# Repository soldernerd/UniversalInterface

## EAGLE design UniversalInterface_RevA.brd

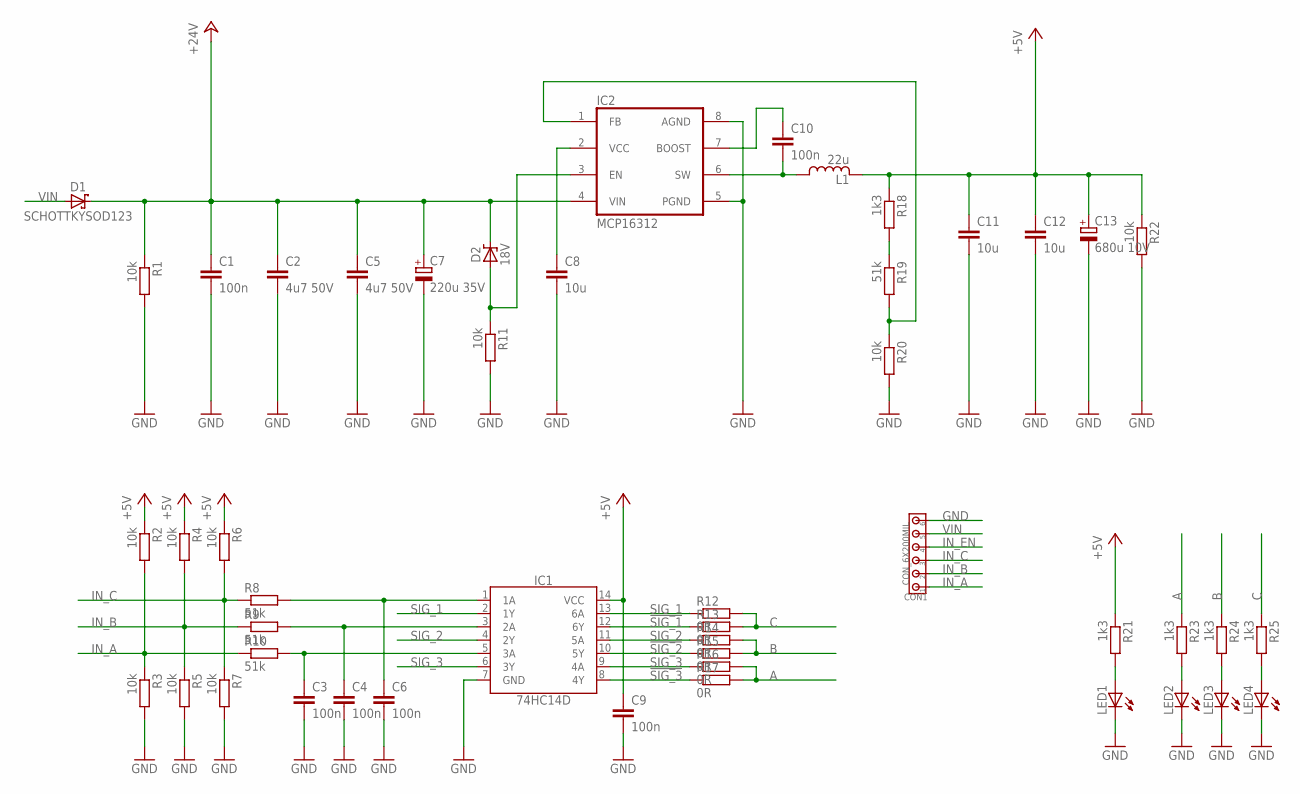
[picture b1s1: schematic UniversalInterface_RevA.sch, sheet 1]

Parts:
C1, C3, C4, C6, C9, C10: 100n; C0805
C2, C5: 4u7 50V; C1206
C7: 220u 35V; 8MM
C8, C11, C12: 10u; C0805
C13: 680u 10V; 8MM
CON1: CON_6X200MIL; 200MIL_6X
D1: SCHOTTKYSOD123; SOD123
D2: 18V; SOD323
IC1: 74HC14D; SO14
IC2: MCP16312; MSOP8
L1: 22u; LPS4018
LED1, LED2, LED3, LED4: LED0805_NB; LED0805_NOBOARDER
R1, R2, R3, R4, R5, R6, R7, R11, R20, R22: 10k; R0805
R8, R9, R10, R19: 51k; R0805
R12, R13, R14, R15, R16, R17: 0R; R0805
R18, R21, R23, R24, R25: 1k3; R0805

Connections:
!SIG_1!: IC1.12 (6Y), R13.1
!SIG_2!: IC1.10 (5Y), R15.1
!SIG_3!: IC1.8 (4Y), R17.1
+5V: C9.1, C11.1, C12.1, C13.+, IC1.14 (VCC), L1.2, R2.1, R4.1, R6.1, R18.1, R21.1, R22.1; also elsewhere on the board
+24V: C1.1, C2.1, C5.1, C7.+, D1.C, D2.C, IC2.4 (VIN), R1.1; also elsewhere on the board
A: R16.2, R17.2, R23.1; also elsewhere on the board
B: R14.2, R15.2, R24.1; also elsewhere on the board
BOOST: C10.1, IC2.7 (BOOST)
C: R12.2, R13.2, R25.1; also elsewhere on the board
FOO: C3.1, IC1.5 (3A), R10.2
GND: C1.2, C2.2, C3.2, C4.2, C5.2, C6.2, C7.-, C8.2, C9.2, C11.2, C12.2, C13.-, CON1.6, IC1.7 (GND), IC2.5 (PGND), IC2.8 (AGND), LED1.C, LED2.C, LED3.C, LED4.C, R1.2, R3.2, R5.2, R7.2, R11.2, R20.2, R22.2; also elsewhere on the board
IN_A: CON1.1, R2.2, R3.1, R10.1
IN_B: CON1.2, R4.2, R5.1, R9.1
IN_C: CON1.3, R6.2, R7.1, R8.1
IN_EN: CON1.4; also elsewhere on the board
unnamed: IC2.1 (FB), R19.2, R20.1
unnamed: LED1.A, R21.2
unnamed: D2.A, IC2.3 (EN), R11.1
unnamed: R18.2, R19.1
unnamed: C8.1, IC2.2 (VCC)
unnamed: LED2.A, R23.2
unnamed: LED3.A, R24.2
unnamed: LED4.A, R25.2
unnamed: C6.1, IC1.1 (1A), R8.2
unnamed: C4.1, IC1.3 (2A), R9.2
SIG_1: IC1.2 (1Y), IC1.13 (6A), R12.1
SIG_2: IC1.4 (2Y), IC1.11 (5A), R14.1
SIG_3: IC1.6 (3Y), IC1.9 (4A), R16.1
SWITCH: C10.2, IC2.6 (SW), L1.1
VIN: CON1.5, D1.A

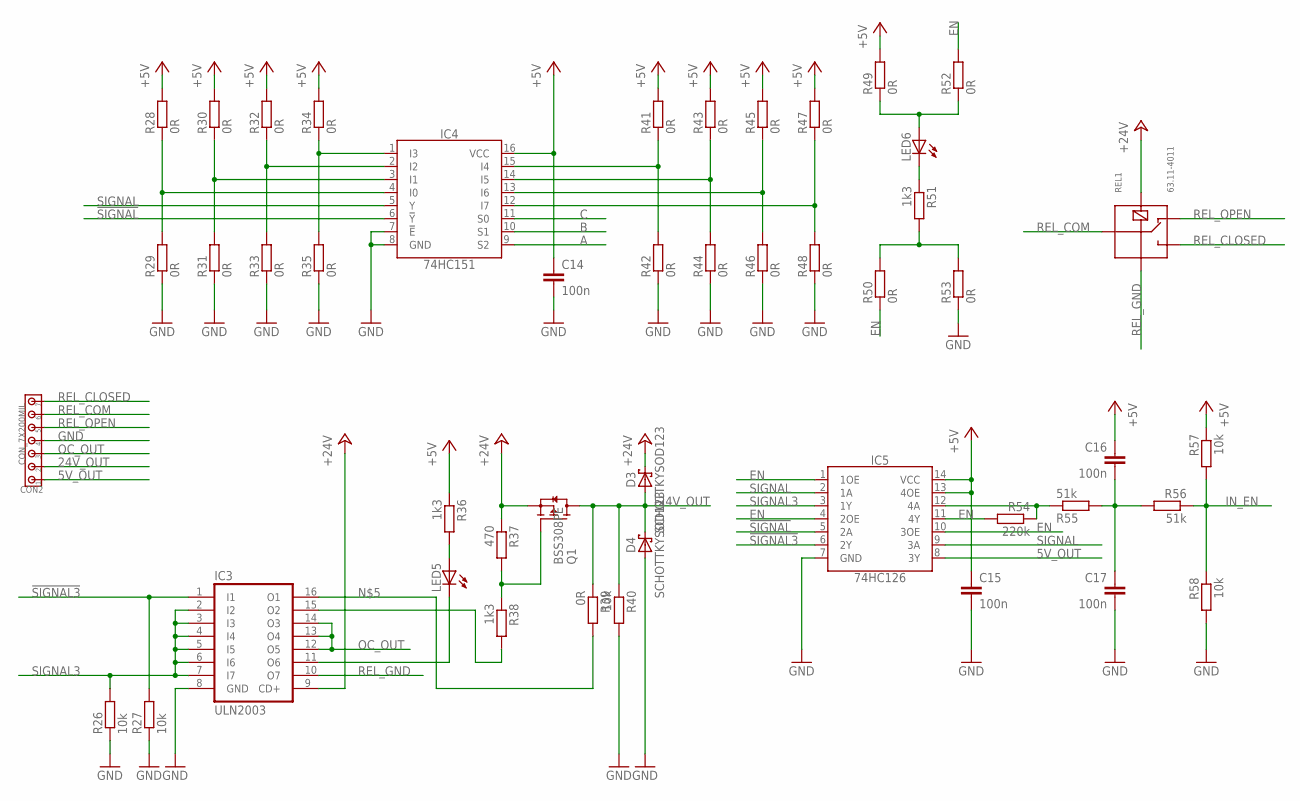
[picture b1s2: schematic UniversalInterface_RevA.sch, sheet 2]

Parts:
C14, C15, C16, C17: 100n; C0805
CON2: CON_7X200MIL; 200MIL_7X
D3, D4: SCHOTTKYSOD123; SOD123
IC3: ULN2003; SO16
IC4: 74HC151; SO16
IC5: 74HC126; SO14
LED5, LED6: LED0805_NB; LED0805_NOBOARDER
Q1: BSS308PE; SOT23
R26, R27, R40, R57, R58: 10k; R0805
R28, R29, R30, R31, R32, R33, R34, R35, R41, R42, R43, R44, R45, R46, R47, R48: 0R; R0805_NOSILK
R36, R38, R51: 1k3; R0805
R37: 470; R0805
R39, R49, R50, R52, R53: 0R; R0805
R54: 220k; R0805
R55, R56: 51k; R0805
REL1: 63.11-4011; G5LE

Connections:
5V_OUT: CON2.1, IC5.8 (3Y)
24V_OUT: CON2.2, D3.A, D4.C, Q1.3 (D), R39.1, R40.1
!SIGNAL3!: IC3.1 (I1), IC5.6 (2Y), R27.2
!SIGNAL!: IC4.6 (!Y!), IC5.5 (2A)
+5V: C14.1, C15.1, C16.1, IC4.16 (VCC), IC5.13 (4OE), IC5.14 (VCC), R28.2, R30.2, R32.2, R34.2, R36.1, R41.2, R43.2, R45.2, R47.2, R49.2, R57.1; also elsewhere on the board
+24V: D3.C, IC3.9 (CD+), Q1.2 (S), R37.1, REL1.2; also elsewhere on the board
A: IC4.9 (S2); also elsewhere on the board
B: IC4.10 (S1); also elsewhere on the board
C: IC4.11 (S0); also elsewhere on the board
EN: IC5.1 (1OE), IC5.4 (2OE), IC5.10 (3OE), IC5.11 (4Y), R50.1, R52.2, R54.2
GND: C14.2, C15.2, C17.2, CON2.4, D4.A, IC3.8 (GND), IC4.7 (!E!), IC4.8 (GND), IC5.7 (GND), R26.1, R27.1, R29.1, R31.1, R33.1, R35.1, R40.2, R42.1, R44.1, R46.1, R48.1, R53.1, R58.2; also elsewhere on the board
I0: IC4.4 (I0), R28.1, R29.2
I1: IC4.3 (I1), R30.1, R31.2
I2: IC4.2 (I2), R32.1, R33.2
I3: IC4.1 (I3), R34.1, R35.2
I4: IC4.15 (I4), R41.1, R42.2
I5: IC4.14 (I5), R43.1, R44.2
I6: IC4.13 (I6), R45.1, R46.2
I7: IC4.12 (I7), R47.1, R48.2
IN_EN: R56.1, R57.2, R58.1; also elsewhere on the board
unnamed: C16.2, C17.1, R55.2, R56.2
unnamed: LED6.C, R51.1
unnamed: IC3.16 (O1), R39.2
unnamed: IC3.11 (O6), LED5.C
unnamed: IC5.12 (4A), R54.1, R55.1
unnamed: LED6.A, R49.1, R52.1
unnamed: LED5.A, R36.2
unnamed: Q1.1 (G), R37.2, R38.1
unnamed: IC3.15 (O2), R38.2
unnamed: R50.2, R51.2, R53.2
OC_OUT: CON2.3, IC3.12 (O5), IC3.13 (O4), IC3.14 (O3)
REL_CLOSED: CON2.7, REL1.C
REL_COM: CON2.6, REL1.COM
REL_GND: IC3.10 (O7), REL1.1
REL_OPEN: CON2.5, REL1.O
SIGNAL: IC4.5 (Y), IC5.2 (1A), IC5.9 (3A)
SIGNAL3: IC3.2 (I2), IC3.3 (I3), IC3.4 (I4), IC3.5 (I5), IC3.6 (I6), IC3.7 (I7), IC5.3 (1Y), R26.2

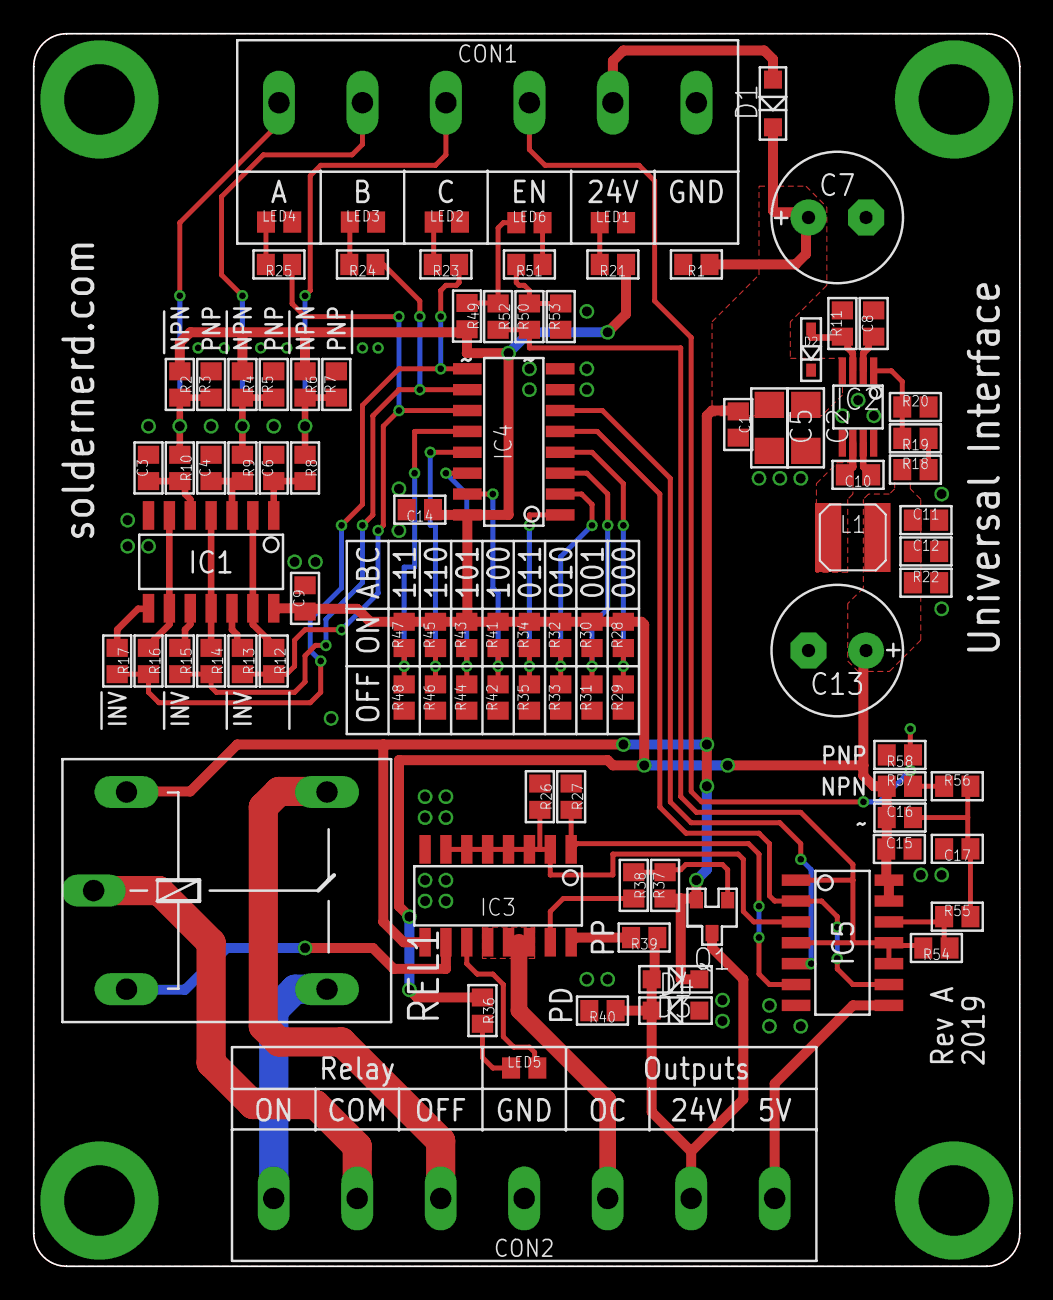
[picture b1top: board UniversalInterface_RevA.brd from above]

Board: 2 copper layers, 60.0 x 75.0 mm, 95 parts (0 on the bottom side), 60 nets.

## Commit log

2019-12-16 Initial commit but already revision B. Revision B is fully functional and tested, there was a minor bug on the revision A board
2019-12-21 PDFs included
2022-01-11 Create LICENSE
